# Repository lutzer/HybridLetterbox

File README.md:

# Hybrid Letterbox

## Installation

* For instructions how to setup the raspberry pi from scratch see file: [docs/pi-installation.md](docs/pi-installation.md)

### Setup Letterbox for the first time

* go to HybridLetterbox dir and update to the newest version: `git pull`
* modify two config files
  * go to src/server/node directory and copy config file: `cp config.defaultjs config.js` and modify file to your needs
  * go to src/letterbox/ and copy ini file: `cp letterbox.default.ini letterbox.ini `  and modify it to your needs

## Development

### Python Test Scripts

* go to src folder and call testscripts by sudo `python2 -m letterbox.tests`

### Node Testscripts

* install pm2 `npm install pm2 -g`

* go to `cd src/www`
  * start testscripts by calling `npm test`

### Configure Atmega Head Board

see  [atmega-installation.md](atmega-installation.md)`

## Update

### 10.9.2016

* edit  `sudo nano /etc/systemd/system/letterbox.service` and change value:

  ```
  RemainAfterExit=false
  ```

* `git pull`

* start admin node script on port 9000

  * `cd src/server/admin/ `

  * `npm install`

  * `cp config.default.js  config.js` and adjust parameters in editor `nano config.js` , these 3 parameters have to be changed:

      ```
      /* AUTH DATA */
      authName: 'admin',
      authPassword: 'password',
      sudoPassword: 'password'
      ```

  * create startup script for admin server: `pm2 start main.js --name LetterboxBackend` and save `pm2 save`

* reboot with `sudo reboot`

* access admin backend by going to `192.168.72.2:9000` within your browser

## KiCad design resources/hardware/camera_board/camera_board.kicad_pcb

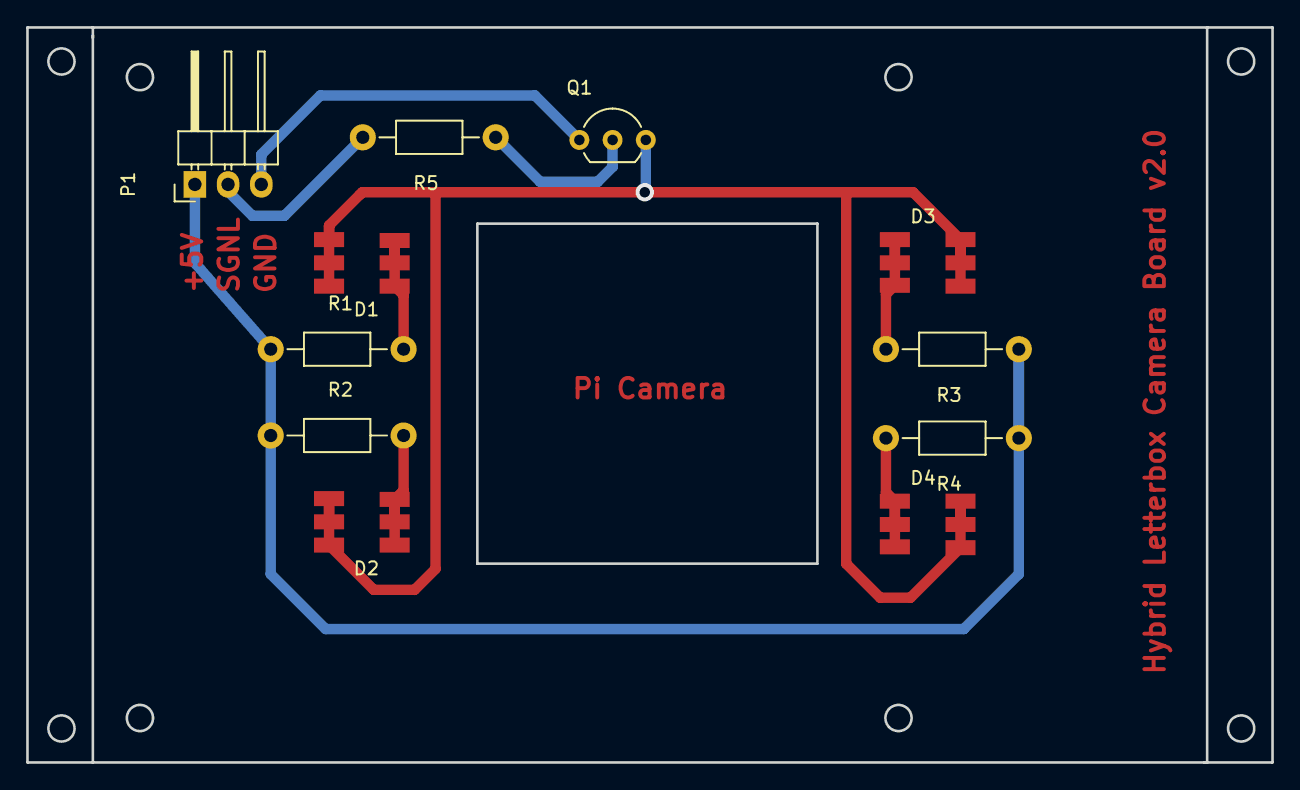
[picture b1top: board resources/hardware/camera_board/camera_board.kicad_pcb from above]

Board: 2 copper layers, 95.2 x 56.2 mm, 11 parts (0 on the bottom side), 9 nets.

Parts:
D1, D2, D3, D4: LED_RGB; SMD-LED_5250
P1: CONN_01X03; Pin_Header_Angled_1x03
Q1: Q_NPN_EBC; TO-92_Inline_Wide
R1, R2, R3, R4, R5: R_Small; Resistor_Horizontal_RM10mm

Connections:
+5V: P1.1, R1.1, R2.1, R3.1, R4.1
/SGNL: P1.2, R5.2
GND: P1.3, Q1.1
unnamed: D1.1, D1.2, D1.3, D2.1, D2.2, D2.3, D3.1, D3.2, D3.3, D4.1, D4.2, D4.3, Q1.3
unnamed: D1.4, D1.5, D1.6, R1.2
unnamed: D2.4, D2.5, D2.6, R2.2
unnamed: D3.4, D3.5, D3.6, R3.2
unnamed: D4.4, D4.5, D4.6, R4.2
unnamed: Q1.2, R5.1

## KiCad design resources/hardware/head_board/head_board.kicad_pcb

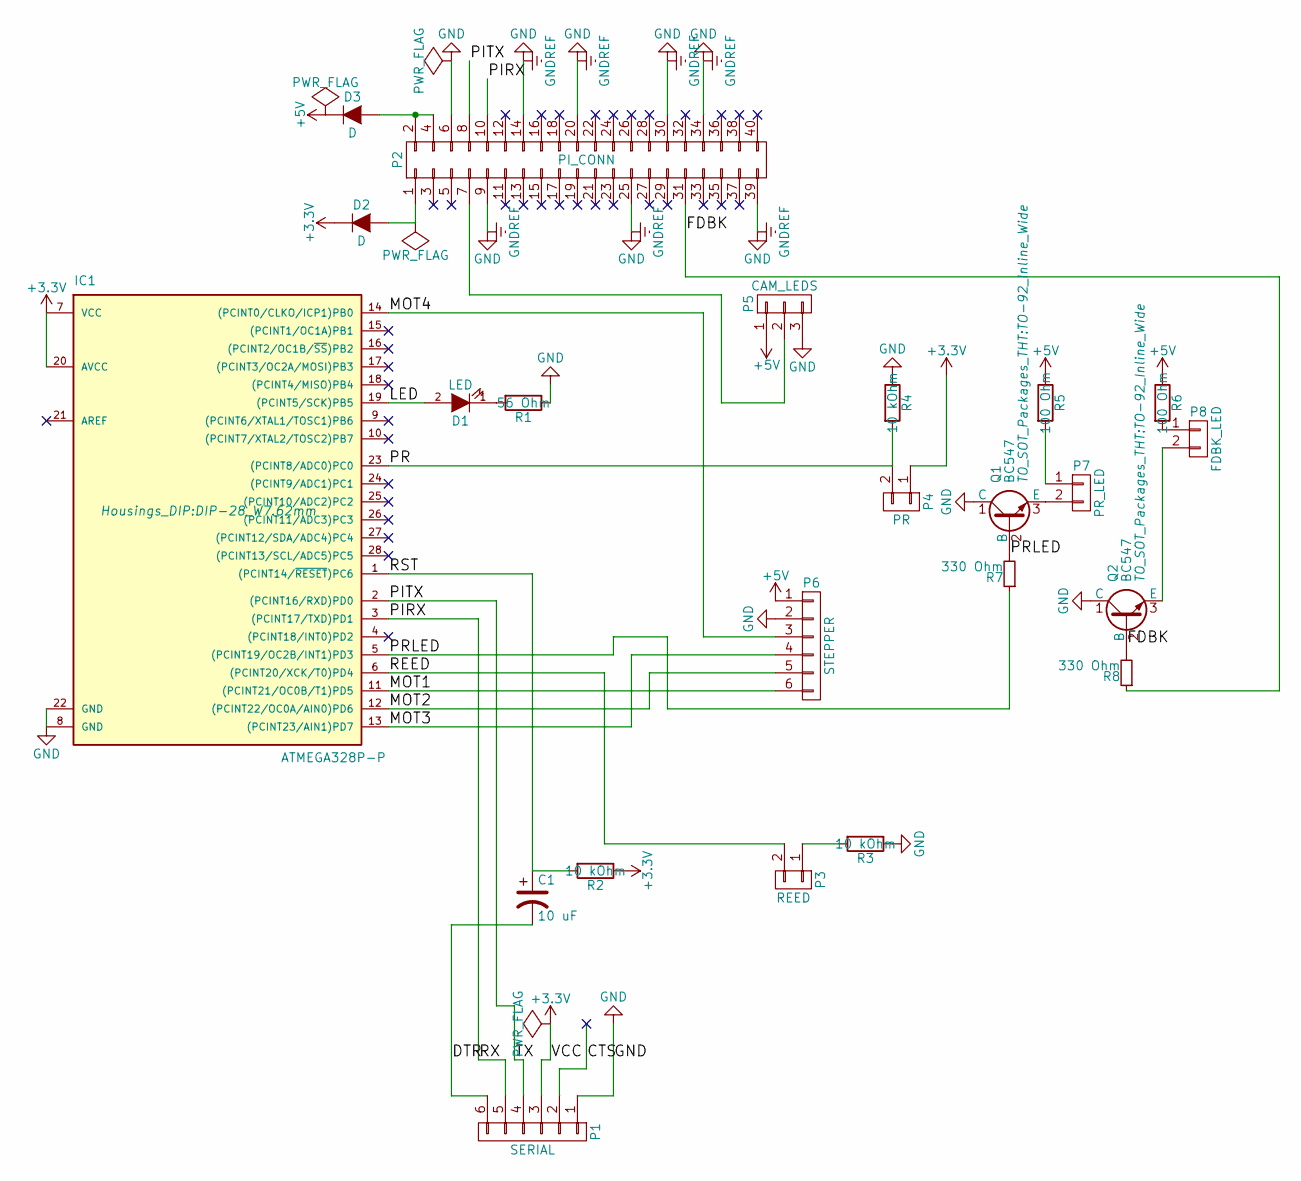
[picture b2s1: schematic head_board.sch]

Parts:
C1: 10 uF; C_Radial_D5_L11_P2
D1: LED; LED-3MM
D2, D3: D; Diode_DO-41_SOD81_Horizontal_RM10
IC1: ATMEGA328P-P; DIP-28_W7.62mm
P1: SERIAL; Pin_Header_Straight_1x06
P2: PI_CONN; Pin_Header_Straight_2x20
P3: REED; Pin_Header_Straight_1x02
P4: PR; Pin_Header_Straight_1x02
P5: CAM_LEDS; Pin_Header_Straight_1x03
P6: STEPPER; Pin_Header_Straight_1x06
P7: PR_LED; Pin_Header_Straight_1x02
P8: FDBK_LED; Pin_Header_Straight_1x02
Q1, Q2: BC547; TO-92_Inline_Wide
R1: 56 Ohm; Resistor_Horizontal_RM7mm
R2, R3, R4: 10 kOhm; Resistor_Horizontal_RM7mm
R5, R6: 100 Ohm; Resistor_Horizontal_RM7mm
R7, R8: 330 Ohm; Resistor_Horizontal_RM7mm

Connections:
+3V3: D2.1 (K), IC1.7 (VCC), IC1.20 (AVCC), P1.3, P4.1, R2.1
+5V: D3.1 (K), P5.1, P6.1, R5.1, R6.1
/DTR: C1.2, P1.6
/FDBK: P2.31, R8.1
/LED: D1.2 (A), IC1.19 ((PCINT5/SCK)PB5)
/MOT1: IC1.11 ((PCINT21/OC0B/T1)PD5), P6.6
/MOT2: IC1.12 ((PCINT22/OC0A/AIN0)PD6), P6.5
/MOT3: IC1.13 ((PCINT23/AIN1)PD7), P6.4
/MOT4: IC1.14 ((PCINT0/CLKO/ICP1)PB0), P6.3
/PIRX: IC1.3 ((PCINT17/TXD)PD1), P1.5, P2.10
/PITX: IC1.2 ((PCINT16/RXD)PD0), P1.4, P2.8
/PR: IC1.23 ((PCINT8/ADC0)PC0), P4.2, R4.2
/PRLED: IC1.5 ((PCINT19/OC2B/INT1)PD3), Q1.2 (B), R7.1, R7.2
/REED: IC1.6 ((PCINT20/XCK/T0)PD4), P3.2
/RST: C1.1, IC1.1 ((PCINT14/~RESET~)PC6), R2.2
GND: IC1.8 (GND), IC1.22 (GND), P1.1, P2.6, P2.9, P2.14, P2.20, P2.25, P2.30, P2.34, P2.39, P5.3, P6.2, Q1.1 (C), Q2.1 (C), R1.1, R3.1, R4.1
unnamed: D1.1 (K), R1.2
unnamed: D2.2 (A), P2.1
unnamed: D3.2 (A), P2.2, P2.4
unnamed: P2.7, P5.2
unnamed: P3.1, R3.2
unnamed: P7.1, R5.2
unnamed: P7.2, Q1.3 (E)
unnamed: P8.1, R6.2
unnamed: P8.2, Q2.3 (E)
unnamed: Q2.2 (B), R8.2

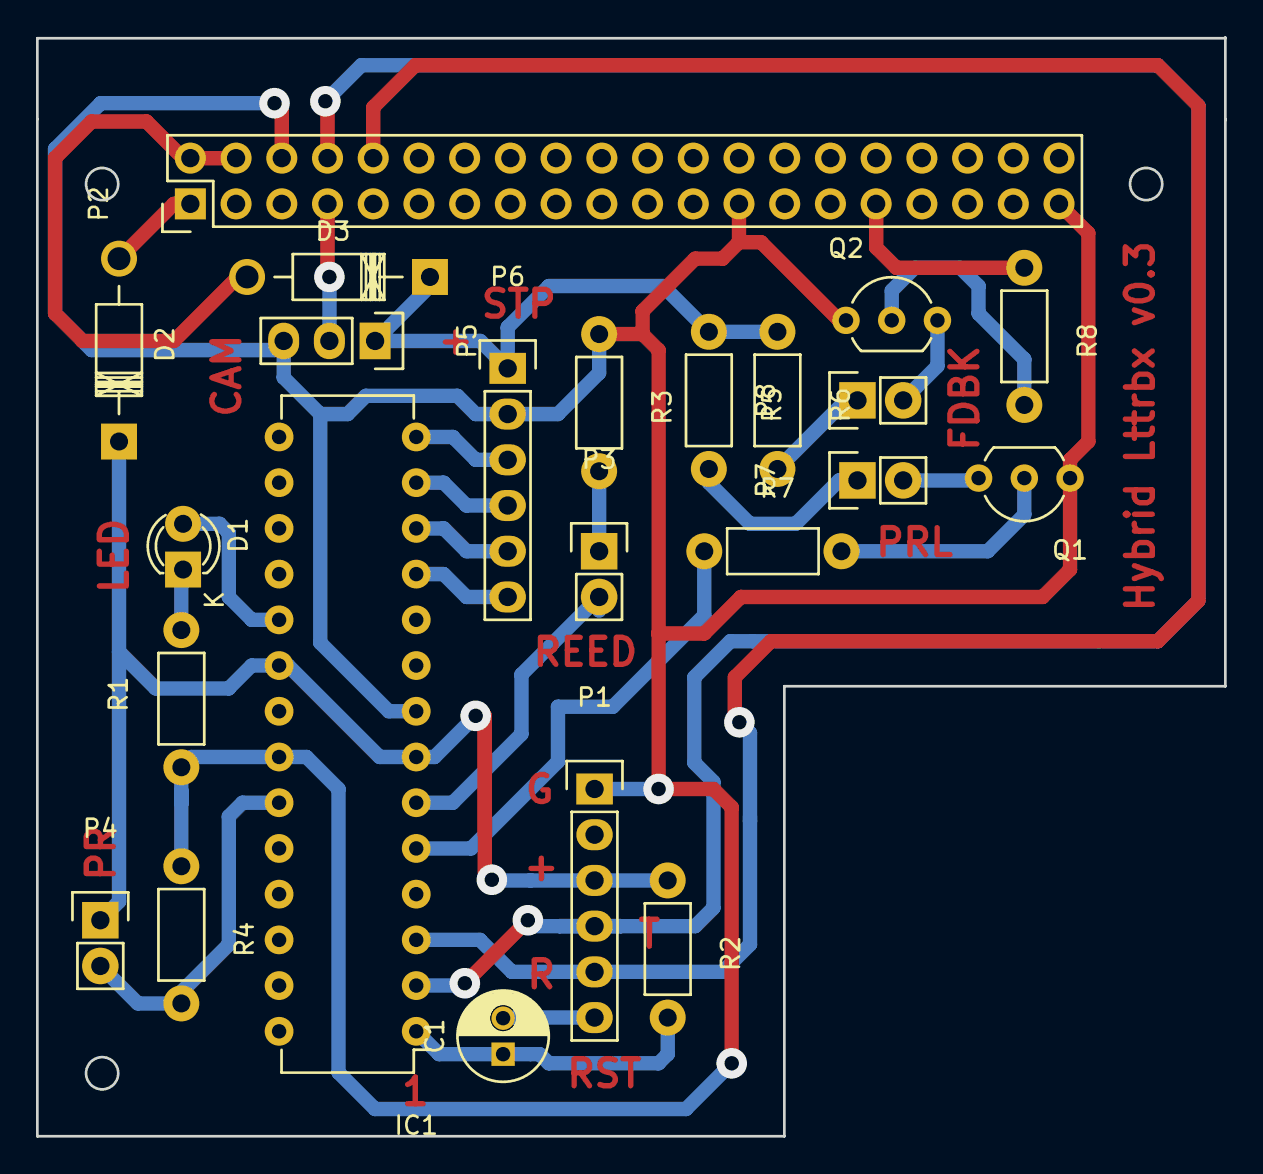
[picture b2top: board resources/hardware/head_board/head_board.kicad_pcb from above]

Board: 2 copper layers, 66.0 x 61.0 mm, 23 parts (0 on the bottom side), 26 nets.

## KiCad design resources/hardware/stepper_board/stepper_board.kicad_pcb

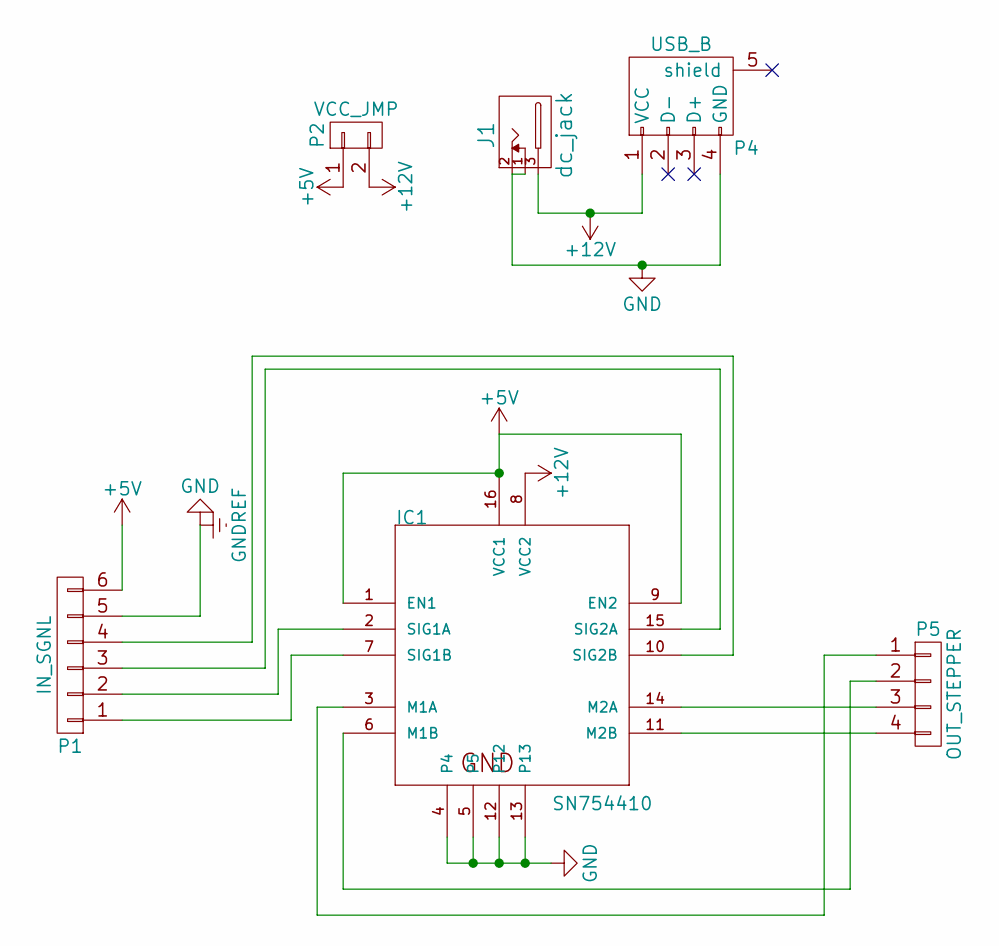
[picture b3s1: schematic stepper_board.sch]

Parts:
IC1: SN754410; DIP-16_W7.62mm
J1: dc_jack; dc_socket
P1: IN_SGNL; Pin_Header_Straight_1x06
P2: VCC_JMP; Pin_Header_Straight_1x02
P4: USB_B
P5: OUT_STEPPER; Pin_Header_Straight_1x04

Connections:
+5V: IC1.1 (EN1), IC1.9 (EN2), IC1.16 (VCC1), P1.6, P2.1
+12V: IC1.8 (VCC2), J1.3, P2.2, P4.1 (VCC)
GND: IC1.4, IC1.5, IC1.12, IC1.13, J1.1, J1.2, P1.5, P4.4 (GND)
unnamed: IC1.2 (SIG1A), P1.2
unnamed: IC1.3 (M1A), P5.1
unnamed: IC1.6 (M1B), P5.2
unnamed: IC1.7 (SIG1B), P1.1
unnamed: IC1.10 (SIG2B), P1.4
unnamed: IC1.11 (M2B), P5.4
unnamed: IC1.14 (M2A), P5.3
unnamed: IC1.15 (SIG2A), P1.3

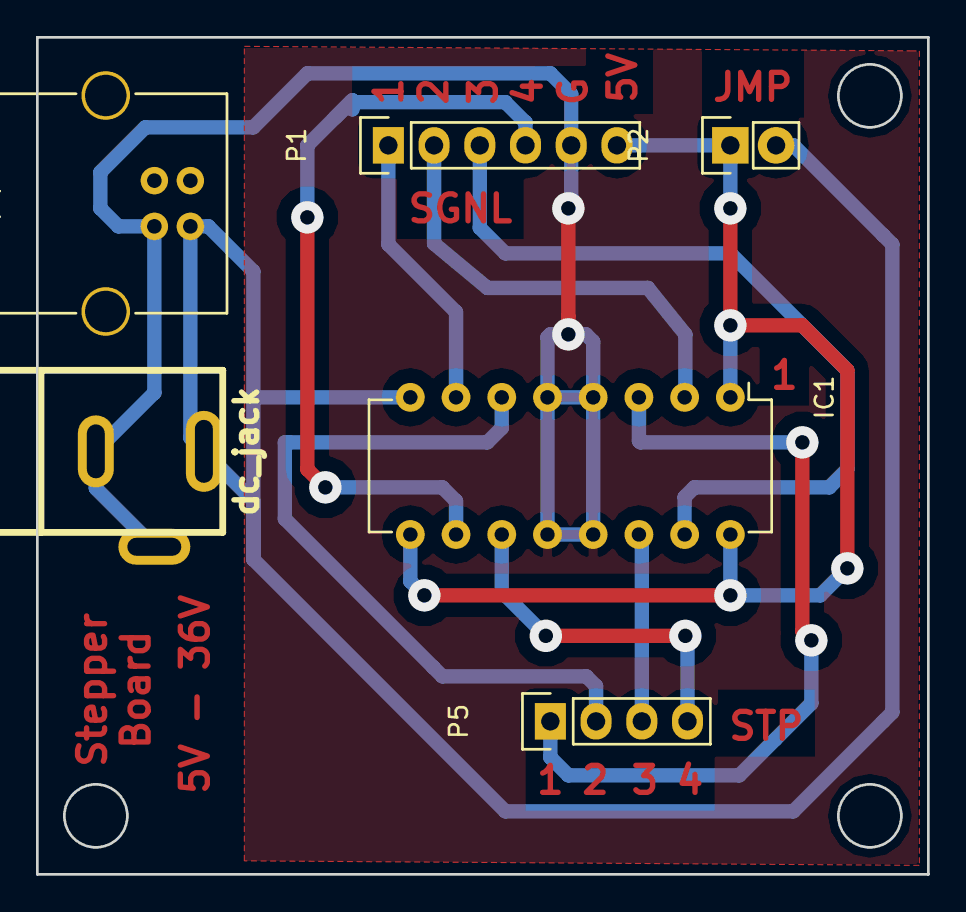
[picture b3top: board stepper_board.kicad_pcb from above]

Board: 2 copper layers, 49.5 x 46.5 mm, 6 parts (0 on the bottom side), 11 nets.

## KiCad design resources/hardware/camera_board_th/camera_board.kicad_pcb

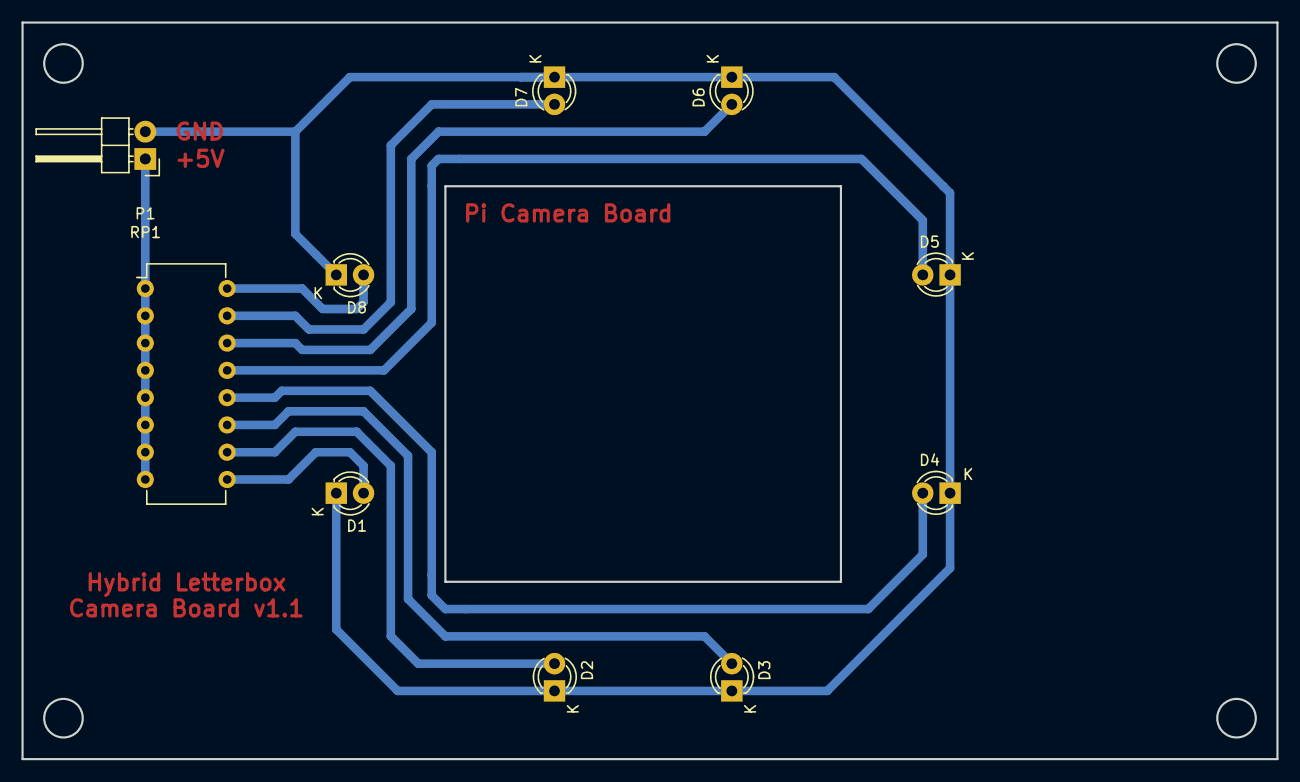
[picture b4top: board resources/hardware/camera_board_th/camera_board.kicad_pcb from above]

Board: 2 copper layers, 116.8 x 68.6 mm, 10 parts (0 on the bottom side), 10 nets.

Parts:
D1, D2, D3, D4, D5, D6, D7, D8: LED; LED-3MM
P1: CONN_01X02; Pin_Header_Angled_1x02
RP1: R_PACK8; DIP-16_W7.62mm

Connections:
+5V: P1.1, RP1.1, RP1.2, RP1.3, RP1.4, RP1.5, RP1.6, RP1.7, RP1.8
GND: D1.1, D2.1, D3.1, D4.1, D5.1, D6.1, D7.1, D8.1, P1.2
unnamed: D1.2, RP1.9
unnamed: D2.2, RP1.10
unnamed: D3.2, RP1.11
unnamed: D4.2, RP1.12
unnamed: D5.2, RP1.13
unnamed: D6.2, RP1.14
unnamed: D7.2, RP1.15
unnamed: D8.2, RP1.16

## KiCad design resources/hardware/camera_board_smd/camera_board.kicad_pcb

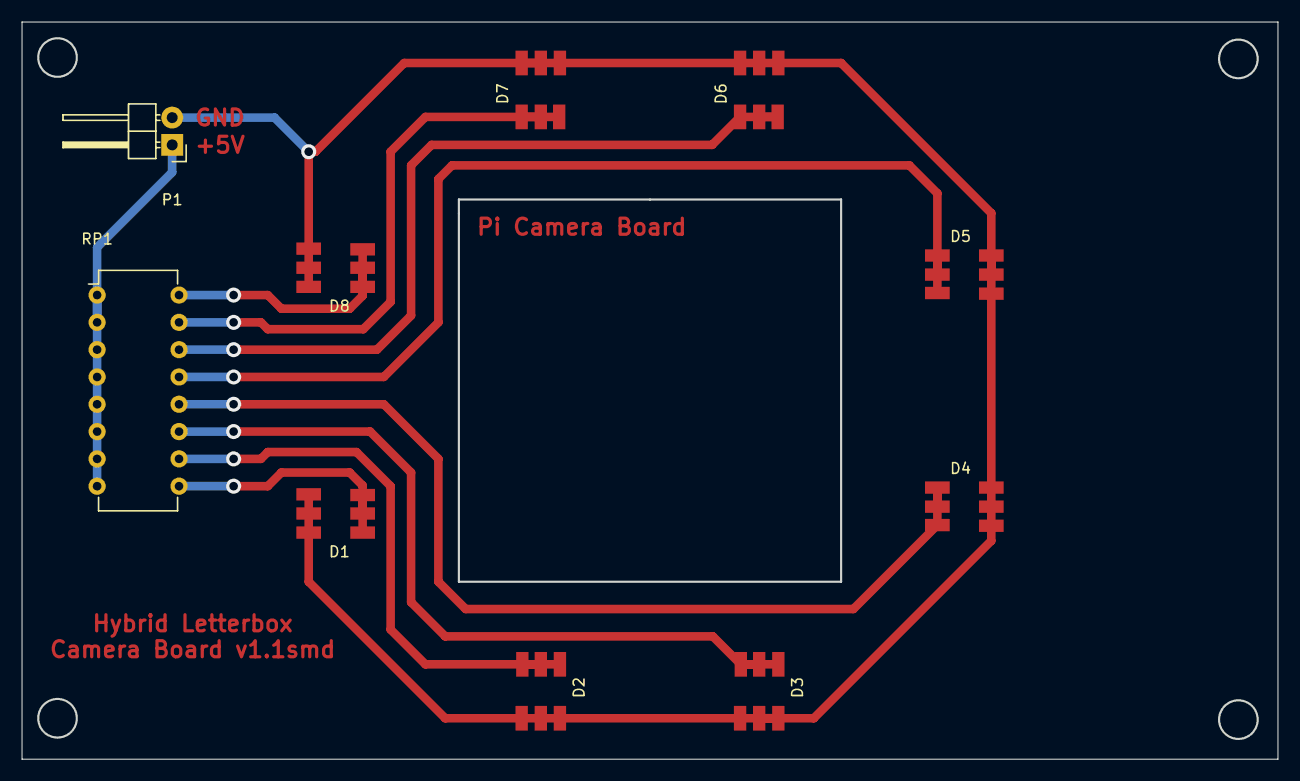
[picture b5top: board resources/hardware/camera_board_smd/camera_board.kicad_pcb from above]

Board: 2 copper layers, 116.8 x 68.6 mm, 10 parts (0 on the bottom side), 10 nets.

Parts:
D1, D2, D3, D4, D5, D6, D7, D8: LED_RGB; SMD-LED_5250
P1: CONN_01X02; Pin_Header_Angled_1x02
RP1: R_PACK8; DIP-16_W7.62mm

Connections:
+5V: P1.1, RP1.1, RP1.2, RP1.3, RP1.4, RP1.5, RP1.6, RP1.7, RP1.8
GND: D1.1, D1.2, D1.3, D2.1, D2.2, D2.3, D3.1, D3.2, D3.3, D4.1, D4.2, D4.3, D5.1, D5.2, D5.3, D6.1, D6.2, D6.3, D7.1, D7.2, D7.3, D8.1, D8.2, D8.3, P1.2
unnamed: D1.4, D1.5, D1.6, RP1.9
unnamed: D2.4, D2.5, D2.6, RP1.10
unnamed: D3.4, D3.5, D3.6, RP1.11
unnamed: D4.4, D4.5, D4.6, RP1.12
unnamed: D5.4, D5.5, D5.6, RP1.13
unnamed: D6.4, D6.5, D6.6, RP1.14
unnamed: D7.4, D7.5, D7.6, RP1.15
unnamed: D8.4, D8.5, D8.6, RP1.16

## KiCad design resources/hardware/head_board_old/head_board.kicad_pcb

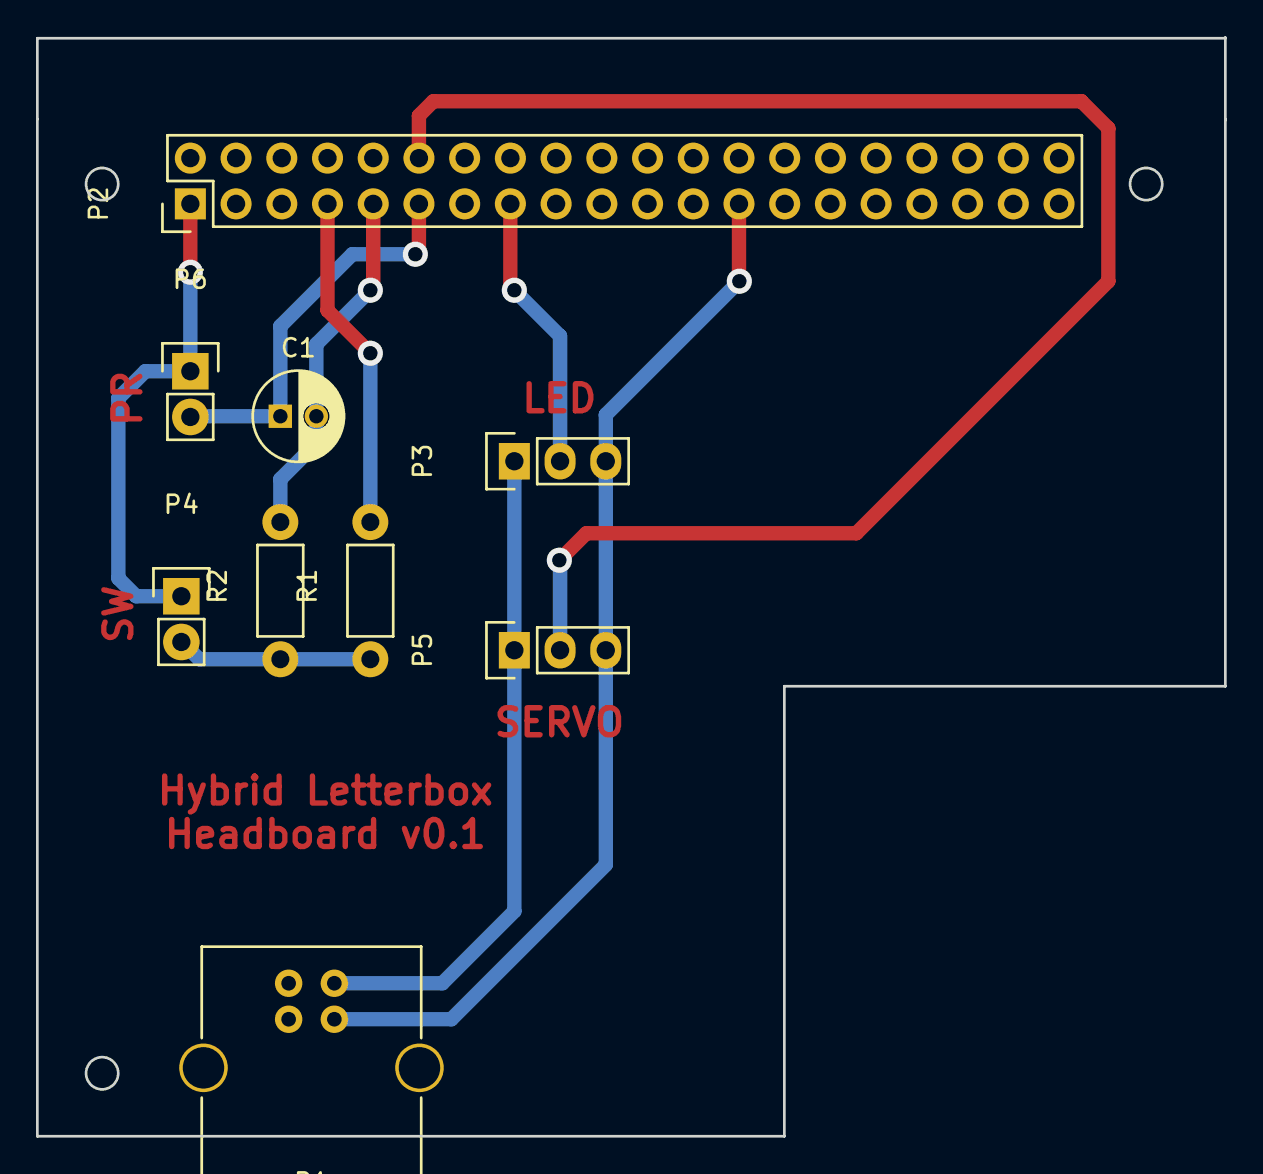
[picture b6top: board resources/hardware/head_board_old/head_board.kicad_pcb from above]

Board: 2 copper layers, 66.0 x 61.0 mm, 9 parts (0 on the bottom side), 8 nets.

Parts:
C1: 1uF 50V; C_Radial_D5_L11_P2
P1: USB_B
P2: PI_CONN; Pin_Header_Straight_2x20
P3: LED; Pin_Header_Straight_1x03
P4: SWITCH; Pin_Header_Straight_1x02
P5: SERVO; Pin_Header_Straight_1x03
P6: PHOTORESISTOR; Pin_Header_Straight_1x02
R1: 1 kOhm; Resistor_Horizontal_RM7mm
R2: 10 kOhm; Resistor_Horizontal_RM7mm

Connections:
+3V3: P2.1, P2.17, P4.1, P6.1
+5V: P1.1, P3.1, P5.1
GND: C1.2, P1.4, P2.6, P2.9, P2.14, P2.20, P2.25, P2.30, P2.34, P2.39, P3.3, P5.3, R2.2
unnamed: C1.1, P2.11, P6.2
unnamed: P2.7, R1.2
unnamed: P2.12, P5.2
unnamed: P2.15, P3.2
unnamed: P4.2, R1.1, R2.1

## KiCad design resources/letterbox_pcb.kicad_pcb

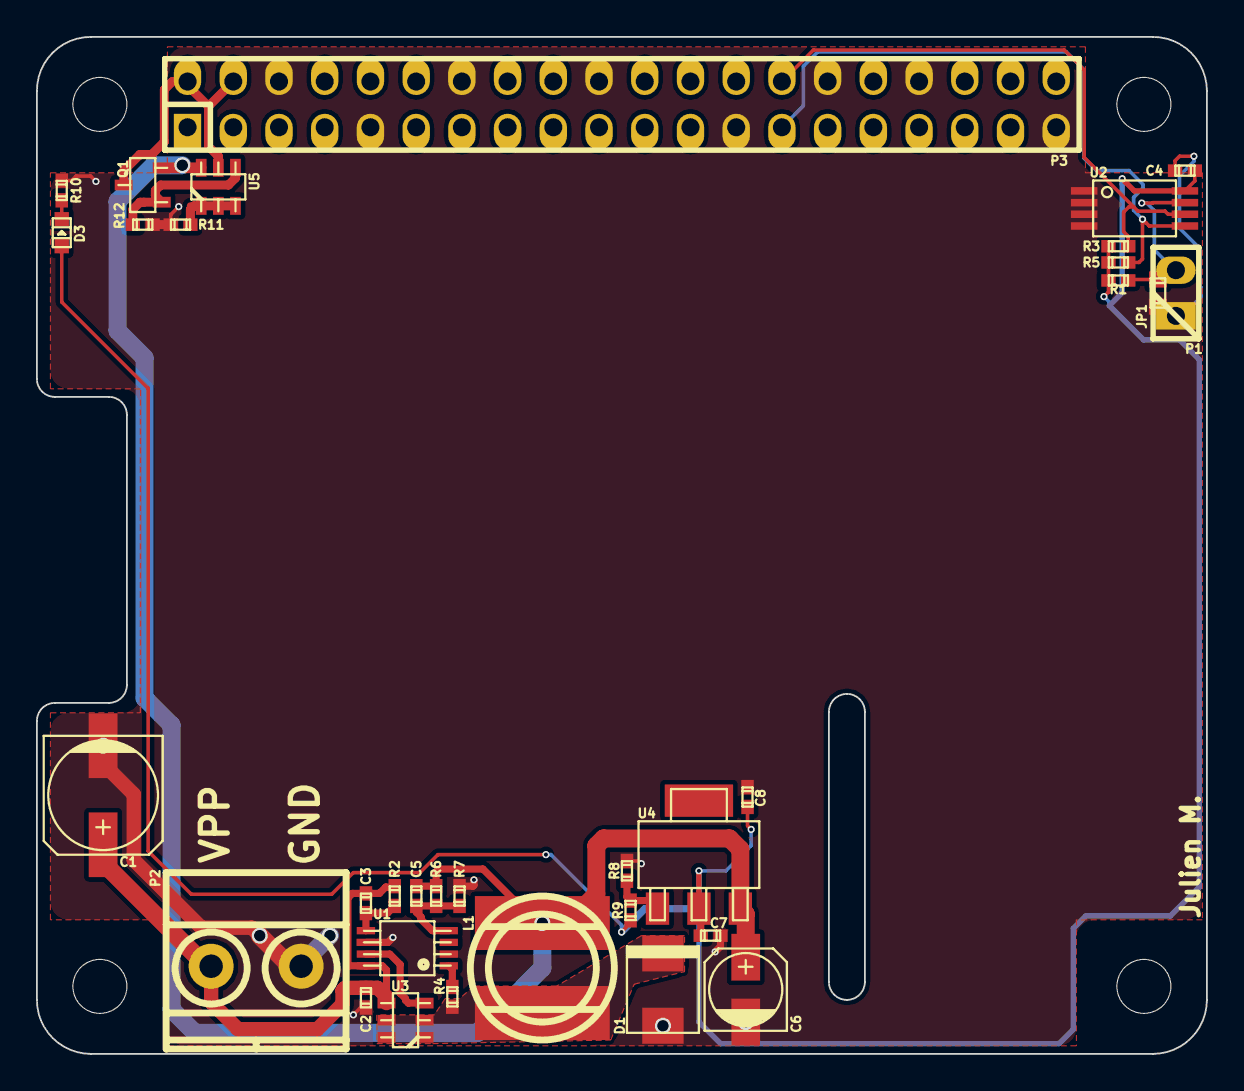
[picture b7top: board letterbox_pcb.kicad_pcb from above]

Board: 2 copper layers, 65.0 x 56.5 mm, 33 parts (0 on the bottom side), 17 nets.

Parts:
C1: 50uf/50v; c_elec_6.3x7.7
C2, C4, C5, C7: 0.1uf; c_0402
C3: 1nf; c_0402
C6: 10uf/6.3V; c_elec_4x5.3
C8: 1uf; c_0402
D1: DIODESCH; do214aa
D3: LED; Led_0603
JP1: JUMPER; r_0603
L1: 22uH; inductor_smd_8x5mm
P1: CONN_01X02; pin_strip_2
P2: CONN_01X02; mkds_1,5-2
P3: Raspberry_Pi_+_Conn; pin_socket_20x2
Q1: BSS138; sot23
R1: 1k; r_0402
R2: 24k; r_0402
R3, R5: 3.9k; r_0402
R4: 270; r_0402
R6: 30k; r_0402
R7, R11: 10k; r_0402
R8: 390; r_0402
R9: 240; r_0402
R10: 360; r_0402
R12: 47k; r_0402
U1: LM3489; msoic-8
U2: CAT24C32HU4I-GT3; tssop-8
U3: FDC5614P; sot23-6
U4: LM1117IMPX-ADJ; sot223
U5: DMMT5401; sot23-6

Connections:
+3V3: C4.1, C7.1, C8.1, D3.1, R1.1, R3.1, R5.1, R9.1, U2.8, U4.2
+5V: C5.1, C6.1, L1.2, Q1.3, R6.1, U4.3, U5.6
+24V: C1.1, C2.1, C3.1, P2.1, R2.1, U1.8, U3.4
/Back Power Protection/5V_MCU: P3.2, P3.4, Q1.2, U5.5
GND: C1.2, C2.2, C4.2, C6.2, C7.2, C8.2, D1.1, JP1.2, P1.1, P2.2, P3.6, P3.9, P3.14, P3.20, P3.25, P3.30, P3.34, P3.39, R7.2, R8.2, R10.2, R11.2, R12.2, U1.2, U1.6, U2.1, U2.2, U2.3, U2.4
unnamed: C3.2, R2.2, U1.5
unnamed: C5.2, R6.2, R7.1, U1.4
unnamed: D1.2, L1.1, R4.1, U3.1, U3.2, U3.5, U3.6
unnamed: D3.2, R10.1
unnamed: JP1.1, P1.2, R1.2, U2.7
unnamed: P3.27, R5.2, U2.5
unnamed: P3.28, R3.2, U2.6
unnamed: Q1.1, R12.1, U5.4
unnamed: R4.2, U1.1
unnamed: R8.1, R9.2, U4.1
unnamed: R11.1, U5.1, U5.2, U5.3
unnamed: U1.7, U3.3

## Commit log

2016-01-11 added read
2016-01-13 added installation instructions
2016-01-13 added hardware specs
2016-01-18 added kicad template
2016-02-04 added first version of came pcbs
2016-02-08 added new pcb version of camera board for wired leds
2016-02-08 no message
2016-02-11 changed pcb layout, changed installation instructions
2016-02-11 removed pihat template
2016-02-11 changed dir structure
2016-02-17 changed pcbs designs
2016-02-20 added attiny doc
2016-02-25 added lasercut sketches for outer frame
2016-03-01 added first sketch for headboard, made some changes on outer frame
2016-03-02 added photocell.h and minstepper.h
2016-03-02 work on minStepper class
2016-03-09 new version of headband sketch, reworked camera board on 4 led version
2016-03-16 new designs for pcbs
2016-03-16 cleaned up hardware folder
2016-03-21 reorganised master branch, added camera calibration code
2016-03-21 added pdf templates for calibration postcards
2016-03-21 reorganised folders
2016-03-24 added letterbox-setup.py
2016-03-29 wrote serial thread python class
2016-03-29 removed pyc files
2016-03-30 serial communication is working
2016-03-30 added stepper communication
2016-03-31 created CameraCalibrator
2016-03-31 blink led
2016-03-31 fixed bug
2016-03-31 reorganised tests
2016-03-31 write first test
2016-03-31 added testcripts
2016-03-31 changed resize docs
2016-03-31 deleted tests.py
2016-03-31 preview is working
2016-04-01 added unittests
2016-04-01 changed tests
2016-04-03 reorganized code
2016-04-03 renamed dir
2016-04-03 changed read
2016-04-03 changed docs
2016-04-04 changed headboard sketch
2016-04-04 added calibration setup script
2016-04-13 fixed test bugs
2016-04-13 added scanning function to setup script
2016-04-14 wrote threshold, extractRegion and findMarker for cardScanner class
2016-04-14 added image
2016-04-14 pattern
2016-04-26 added pattern scanner
2016-04-26 reverse commit
2016-04-26 cleaned up repo
2016-04-26 refactoring
2016-04-26 refactor
2016-04-26 added undistort script
2016-04-27 changed directory structure
2016-04-27 created initial letterbox script
2016-04-27 addes initial server commit
2016-04-27 del .sass-cache
2016-04-27 created initial unit tests for node server
2016-04-27 added user tests to node server
2016-04-27 added node socket.io unit tests
2016-04-27 added server
2016-04-28 changed file structure
2016-04-28 changed test database location
2016-04-28 added feedback socket
2016-04-29 added sync db tests
2016-05-02 mongodb database Anbindung
2016-05-02 changed to mongoose
2016-05-02 changed www dir
2016-05-03 created es6-babel boilerplate for tablet interface
2016-05-03 es6 backbone boilerplates
2016-05-03 removed js folder from repo
2016-05-03 updated read files
2016-05-03 modified npm dependencies
2016-05-04 added comment function to server, wrote first frontend classes
2016-05-04 db connection fix, reorganized dirs
2016-05-04 fixed test timeout
2016-05-05 cleaned app entry point
2016-05-05 added database connection test
2016-05-05 refactor www/app.js code
2016-05-05 bugfix
2016-05-05 implementing file upload
2016-05-05 cleaned router code
2016-05-06 fixed tests
2016-05-06 added file upload function
2016-05-06 finished file upload testing and implementation
2016-05-07 cleaned up error handling
2016-05-07 cleaned up tests
2016-05-09 added files folder
2016-05-09 added _tmp dir
2016-05-09 added default config
2016-05-09 added user authentication for delete routes, prevent editing on post routes
2016-05-09 implemented authentification and tags
2016-05-09 writing on updating submissions
2016-05-09 fixed PUT submission route (update)
2016-05-10 bug fixing, escape database, started working on frontend
2016-05-10 some bug fixes in node server + comment add and comment deletion in frontend
2016-05-10 escape html characters, but recursive escaping in nested string arrays is still failing
2016-05-11 added validation and fixed escaping strings
2016-05-11 started styling web
2016-05-17 changed sass
2016-05-24 use strict & added single view
2016-05-24 fixed comment input view
2016-05-26 implemening iframe transport
2016-05-26 iframe upload finished, sass style changes
2016-05-27 added tag input in fronted
2016-05-29 added pagination
2016-05-30 added spinner, changed layout, bug fixing
2016-05-31 added admin panel
2016-06-02 added stepper board
2016-06-05 finished new headboard pcbs
2016-06-06 deleted old headboard, modified new
2016-06-07 changed dir structure, added request script
2016-06-08 Addis testscripts dir
2016-06-09 adapted to node api
2016-06-09 added submission dir
2016-06-09 changed pr readings
2016-06-09 bugfixes
2016-06-09 blabaal
2016-06-15 added python testclasses to run on desktop
2016-06-15 fixed socket url adress for www app
2016-06-16 fix file upload
2016-06-16 added socket io clien package
2016-06-16 added api description
2016-06-16 changed button shadow
2016-06-17 fixed python file upload
2016-06-20 fixed send submission script
2016-06-20 changed headboard pcbs layout, implemented marker detection, minor bug fixed on www
2016-06-20 added letterbox control class for old prototype
2016-06-20 added old lb control
2016-06-21 created postcard templates, bugfixes
2016-06-21 bugfixes for running on prototype2
2016-06-22 changed marker pattern
2016-06-22 moved device version to ini file
2016-06-22 rotate on flipped
2016-06-22 bugfix rotate
2016-06-22 changed postcard markers
2016-06-22 changed markers
2016-06-22 changed letterbox.ini
2016-06-22 wrote setup script
2016-06-22 added compiled www js files
2016-06-22 added async eject function vor prototype 2
2016-06-22 changed working dir for startup script
2016-06-23 bugfix null tag
2016-06-23 created tablet view
2016-06-23 added horizontal line on logo
2016-06-23 changed responsive sizes
2016-06-23 style changes
2016-06-23 dataset fixes
2016-06-23 revert commit
2016-06-23 added feedback mechanism
2016-06-23 changed scanning feedback style
2016-06-27 fixed scroll load
2016-06-27 added schematic plots
2016-06-28 added pcbs schematics
2016-06-29 bug fixing headboard code: photocell readings
2016-06-30 added dataset parameter on api/submissions/
2016-06-30 changed headboard sketch parameters
2016-06-30 fixed some pcbs issues
2016-07-01 web platform new design
2016-07-05 changed dataset to null
2016-07-05 style fixing
2016-07-11 added drill marks
2016-07-14 added projection view
2016-07-14 disabled auth
2016-07-14 fixed projection
2016-07-14 fixed to show new image in projection
2016-07-24 update docs
2016-07-24 changed calibration script
2016-08-18 added motor test
2016-08-18 added new calibration template card
2016-08-18 changed template
2016-08-24 adopted to new camera
2016-08-24 added twitter function
2016-08-24 changed default ini
2016-08-25 changed letterbox test script
2016-08-25 changed photocell calibration function
2016-08-29 fixed twitter bug
2016-08-29 close button change
2016-08-29 fixed twiter bug
2016-09-01 fixed contrast increase bug
2016-09-11 fixed letterbox service cleanup bug
2016-09-11 admin backend
2016-09-11 fixed sudo command error in admin script
2016-09-11 added logging function to letterbox service
2016-09-11 changed message bar
2016-09-11 added auth function to admin script
2016-09-12 change read
2016-09-12 status message fixes
2019-03-29 Create LICENSE

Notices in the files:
resources/letterbox_pcb.kicad_pcb:
License: CERN OHL V1.2
CERN OHL V1.2
